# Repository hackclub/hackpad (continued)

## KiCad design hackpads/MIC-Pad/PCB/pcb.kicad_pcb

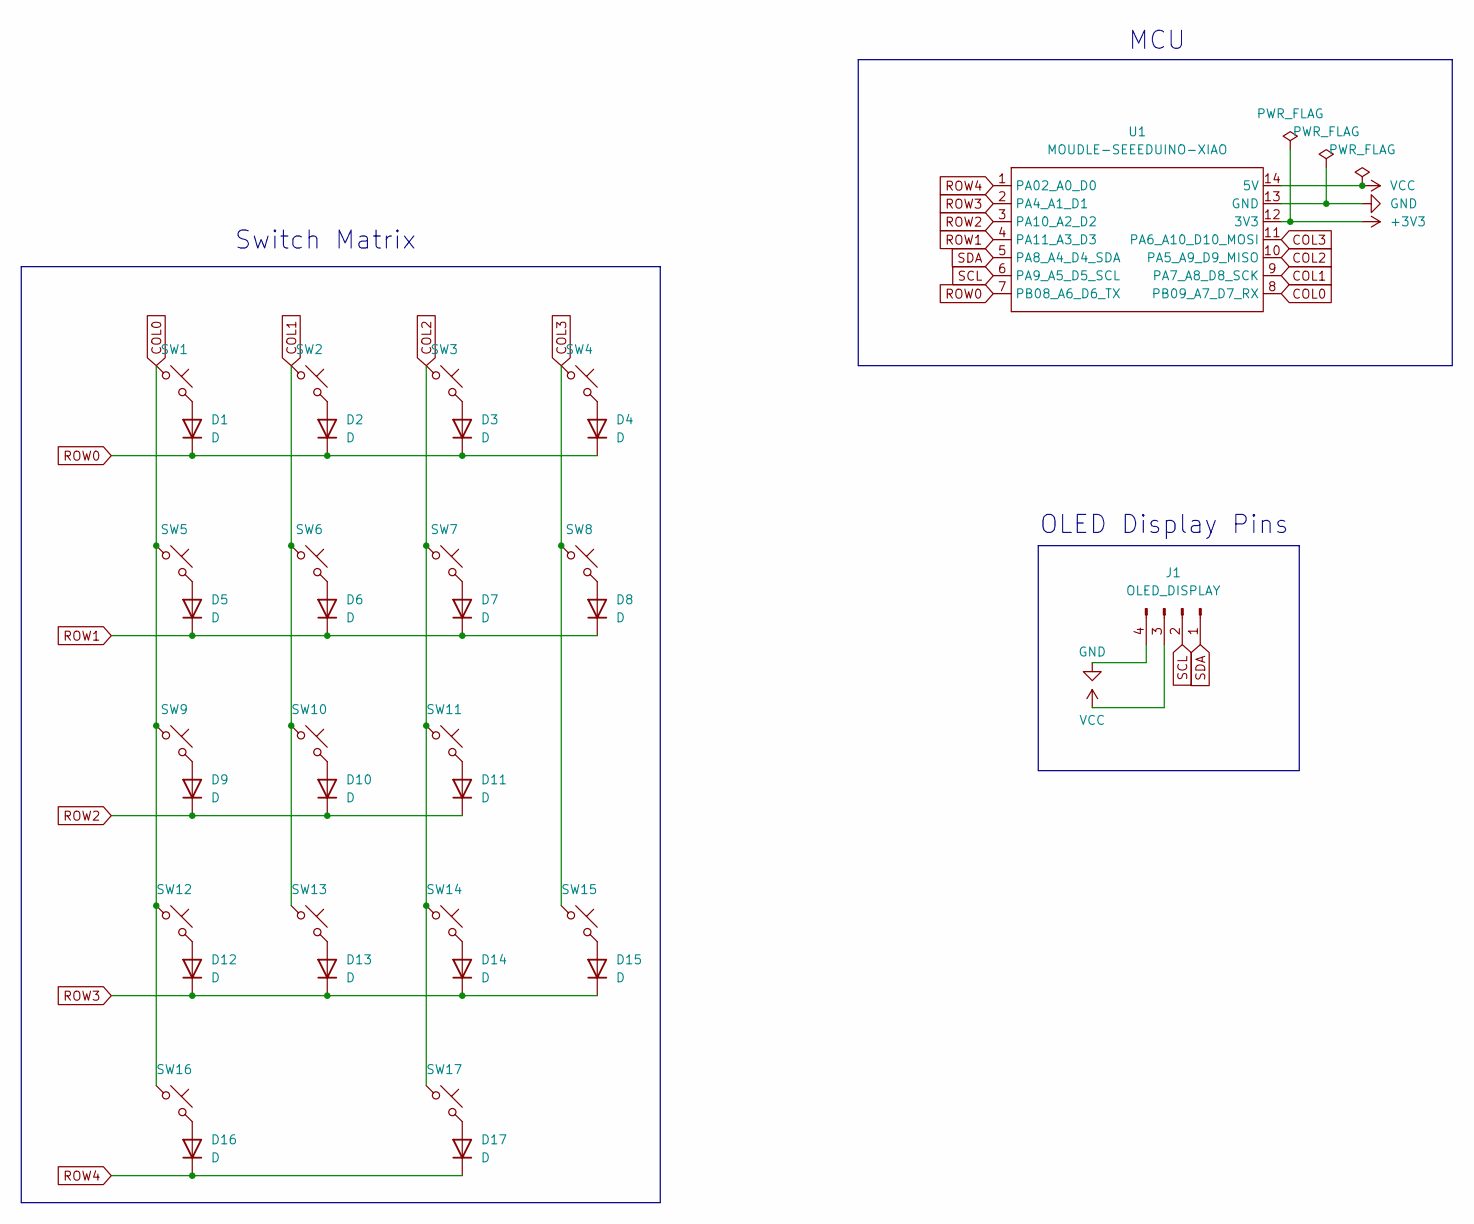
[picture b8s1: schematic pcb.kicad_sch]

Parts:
D1, D2, D3, D4, D5, D6, D7, D8, D9, D10, D11, D12, D13, D14, D15, D16, D17: D; Diode_DO-35
J1: OLED_DISPLAY; PinHeader_1x04_P2.54mm_Vertical
SW1, SW2, SW3, SW4, SW5, SW6, SW7, SW8, SW9, SW10, SW11, SW12, SW13, SW14, SW15, SW16, SW17: SW_Push_45deg; MX-Solderable-1U-3D
U1: MOUDLE-SEEEDUINO-XIAO; XIAO-Generic-Hybrid-14P-2.54-21X17.8MM

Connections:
+3V3: U1.12 (3V3)
COL0: SW1.1, SW5.1, SW9.1, SW12.1, SW16.1, U1.8 (PB09_A7_D7_RX)
COL1: SW2.1, SW6.1, SW10.1, SW13.1, U1.9 (PA7_A8_D8_SCK)
COL2: SW3.1, SW7.1, SW11.1, SW14.1, SW17.1, U1.10 (PA5_A9_D9_MISO)
COL3: SW4.1, SW8.1, SW15.1, U1.11 (PA6_A10_D10_MOSI)
GND: J1.4, U1.13 (GND)
unnamed: D1.2 (A), SW1.2
unnamed: D2.2 (A), SW2.2
unnamed: D3.2 (A), SW3.2
unnamed: D4.2 (A), SW4.2
unnamed: D5.2 (A), SW5.2
unnamed: D6.2 (A), SW6.2
unnamed: D7.2 (A), SW7.2
unnamed: D8.2 (A), SW8.2
unnamed: D9.2 (A), SW9.2
unnamed: D10.2 (A), SW10.2
unnamed: D11.2 (A), SW11.2
unnamed: D12.2 (A), SW12.2
unnamed: D13.2 (A), SW13.2
unnamed: D14.2 (A), SW14.2
unnamed: D15.2 (A), SW15.2
unnamed: D16.2 (A), SW16.2
unnamed: D17.2 (A), SW17.2
ROW0: D1.1 (K), D2.1 (K), D3.1 (K), D4.1 (K), U1.7 (PB08_A6_D6_TX)
ROW1: D5.1 (K), D6.1 (K), D7.1 (K), D8.1 (K), U1.4 (PA11_A3_D3)
ROW2: D9.1 (K), D10.1 (K), D11.1 (K), U1.3 (PA10_A2_D2)
ROW3: D12.1 (K), D13.1 (K), D14.1 (K), D15.1 (K), U1.2 (PA4_A1_D1)
ROW4: D16.1 (K), D17.1 (K), U1.1 (PA02_A0_D0)
SCL: J1.2, U1.6 (PA9_A5_D5_SCL)
SDA: J1.1, U1.5 (PA8_A4_D4_SDA)
VCC: J1.3, U1.14 (5V)

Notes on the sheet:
OLED Display Pins
MCU
Switch Matrix

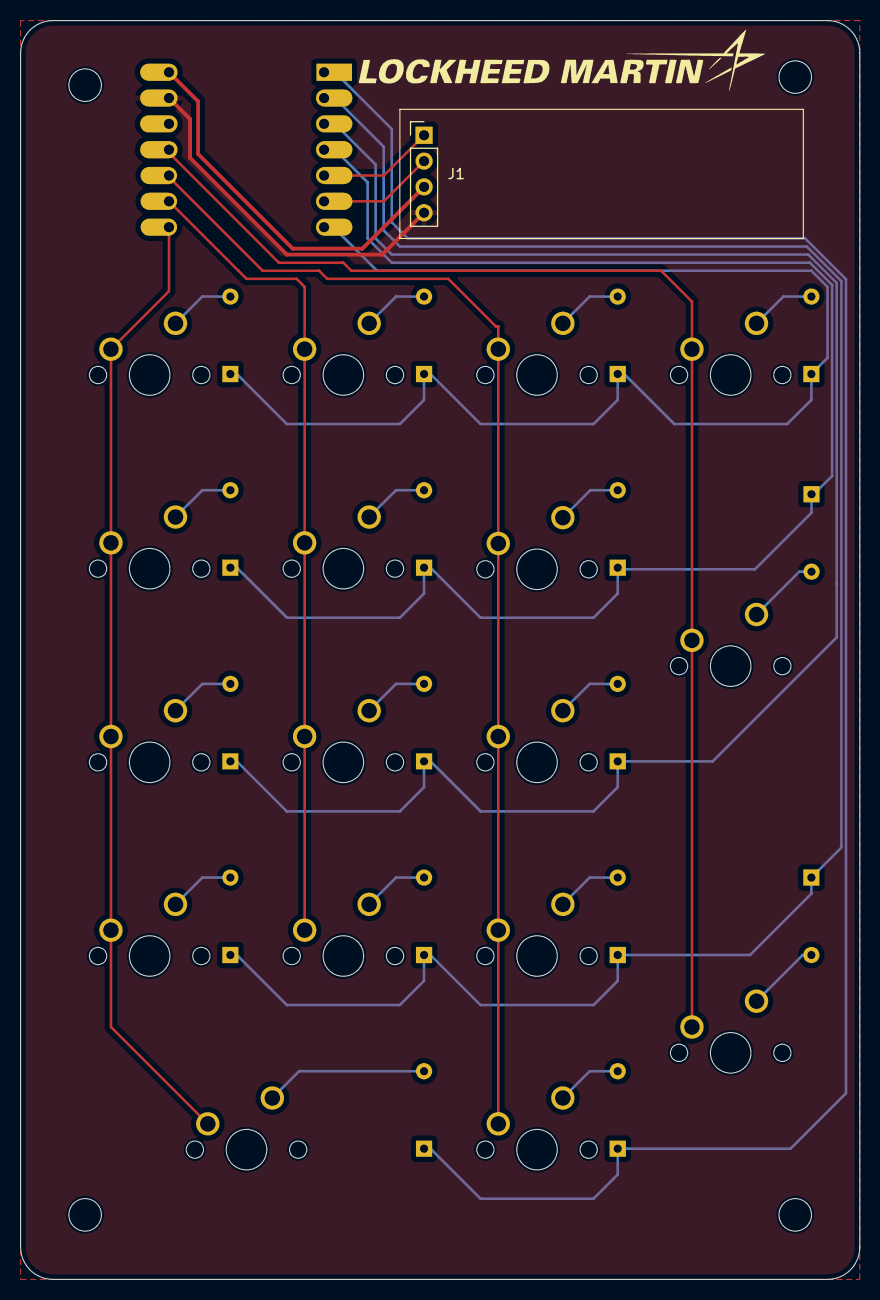
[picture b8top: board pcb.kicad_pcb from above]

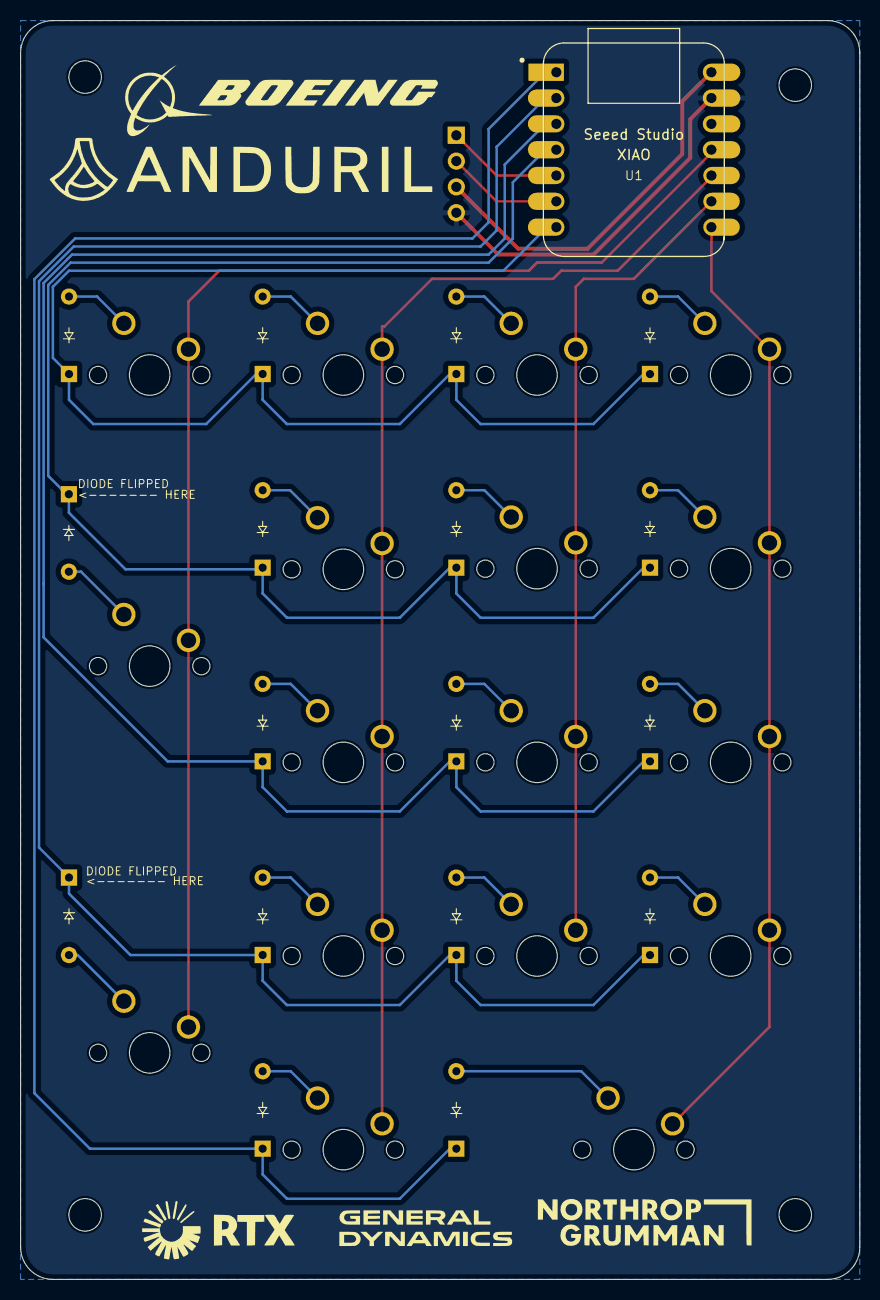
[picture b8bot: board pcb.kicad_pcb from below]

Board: 2 copper layers, 82.5 x 123.8 mm, 36 parts (18 on the bottom side), 30 nets.
